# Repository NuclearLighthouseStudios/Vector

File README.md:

# Vector Hysteresis Distortion

These are the KiCAD schematics and board layout filed for my Vector Hysteresis Distortion pedal.  
If you just want the Gerber files or a PDF of the schematic check out the releases tab for downloads.

This PCB should be easily manufacturable with most online PCB houses by just uploading the gerber files.

This board is designed to be used with my Switchboard Pedal IO PCB which you can find [here](https://github.com/NuclearLighthouseStudios/Switchboard).

## BOM

| Reference       | Quantity | Value  | Description                                          |
| :-------------- | -------: | -----: | :--------------------------------------------------- |
| C1 C3 C5 C6 C7  | 5        | 100n   | WIMA MKS2 63V                                        |
| C2 C8           | 2        | 1µ     | WIMA MKS2 50V                                        |
| C4              | 1        | 470n   | WIMA MKS2 50V                                        |
| D1 D2           | 2        | 1N4148 | DO-35 Diode                                          |
| J1              | 1        |        | Pin Header, 6 pins, 2.54mm spacing                   |
| J2              | 1        |        | DC Barrel Jack with internal switch                  |
| Q1 Q2 Q3 Q4     | 4        | BC547B | 0.1A Ic, 45V Vce, Small Signal NPN Transistor, TO-92 |
| R1 R2 R5 R13    | 4        | 1M     | Metal film resistor 1%, DIN 0207                     |
| R3 R14          | 2        | 10k    | Metal film resistor 1%, DIN 0207                     |
| R4 R7 R8 R9 R12 | 5        | 100k   | Metal film resistor 1%, DIN 0207                     |
| R6 R10          | 2        | 470k   | Metal film resistor 1%, DIN 0207                     |
| R11             | 1        | 22k    | Metal film resistor 1%, DIN 0207                     |
| R15             | 1        | 39k    | Metal film resistor 1%, DIN 0207                     |
| RV1 RV2         | 2        | 100k   | Alps RK09K1130C94 Potentiometer                      |

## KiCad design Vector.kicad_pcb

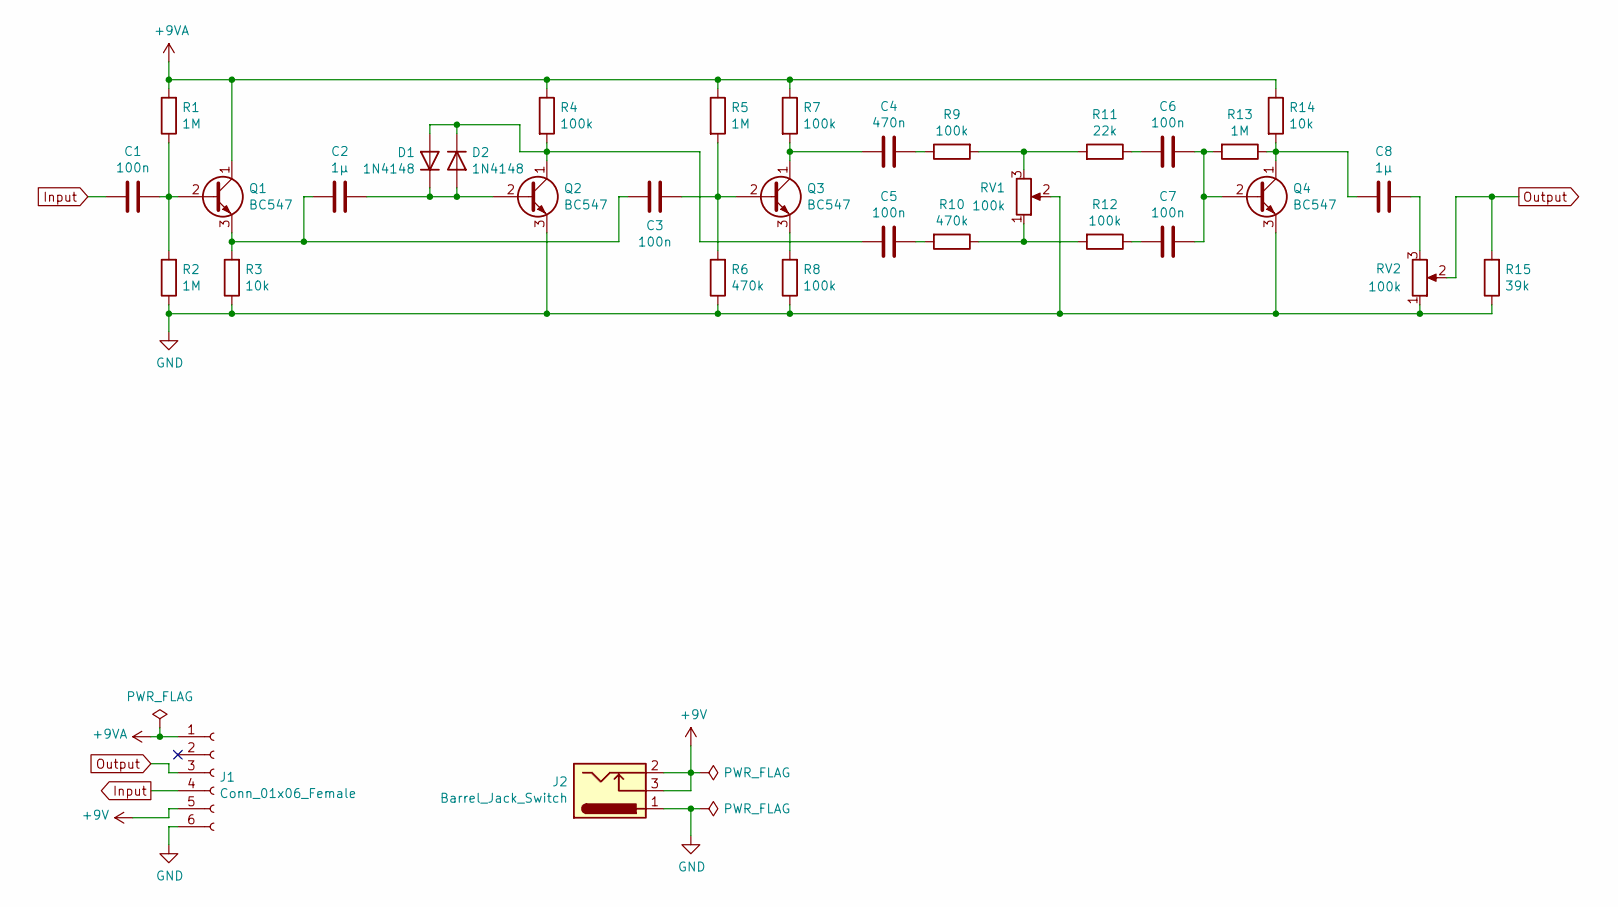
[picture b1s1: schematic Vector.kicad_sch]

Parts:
C1, C3, C5, C6, C7: 100n; C_Rect_L7.2mm_W2.5mm_P5.00mm_FKS2_FKP2_MKS2_MKP2
C2, C8: 1µ; C_Rect_L7.2mm_W4.5mm_P5.00mm_FKS2_FKP2_MKS2_MKP2
C4: 470n; C_Rect_L7.2mm_W3.5mm_P5.00mm_FKS2_FKP2_MKS2_MKP2
D1, D2: 1N4148; D_DO-35_SOD27_P2.54mm_Vertical_AnodeUp
J1: Conn_01x06_Female; PinHeader_1x06_P2.54mm_Vertical
J2: Barrel_Jack_Switch; BarrelJack_Horizontal_Short
Q1, Q2, Q3, Q4: BC547; TO-92_Wide
R1, R2, R5, R13: 1M; R_Axial_DIN0207_L6.3mm_D2.5mm_P2.54mm_Vertical
R3, R14: 10k; R_Axial_DIN0207_L6.3mm_D2.5mm_P2.54mm_Vertical
R4, R7, R8, R9: 100k; R_Axial_DIN0207_L6.3mm_D2.5mm_P2.54mm_Vertical
R6: 470k; R_Axial_DIN0207_L6.3mm_D2.5mm_P2.54mm_Vertical
R10: 470k; R_Axial_DIN0207_L6.3mm_D2.5mm_P7.62mm_Horizontal
R11: 22k; R_Axial_DIN0207_L6.3mm_D2.5mm_P7.62mm_Horizontal
R12: 100k; R_Axial_DIN0207_L6.3mm_D2.5mm_P7.62mm_Horizontal
R15: 39k; R_Axial_DIN0207_L6.3mm_D2.5mm_P7.62mm_Horizontal
RV1, RV2: 100k; Potentiometer_Alps_RK09K_Single_Vertical

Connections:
+9V: J1.5, J2.2, J2.3
+9VA: J1.1, Q1.1 (C), R1.2, R4.1, R5.1, R7.1, R14.1
GND: J1.6, J2.1, Q2.3 (E), Q4.3 (E), R2.1, R3.1, R6.1, R8.1, R15.1, RV1.2, RV2.1
Input: C1.2, J1.4
unnamed: C1.1, Q1.2 (B), R1.1, R2.2
unnamed: C2.1, C3.2, Q1.3 (E), R3.2
unnamed: C2.2, D1.1 (K), D2.2 (A), Q2.2 (B)
unnamed: C3.1, Q3.2 (B), R5.2, R6.2
unnamed: C4.1, R9.1
unnamed: C4.2, Q3.1 (C), R7.2
unnamed: C5.1, R10.2
unnamed: C5.2, D1.2 (A), D2.1 (K), Q2.1 (C), R4.2
unnamed: C6.1, C7.1, Q4.2 (B), R13.2
unnamed: C6.2, R11.1
unnamed: C7.2, R12.1
unnamed: C8.1, RV2.3
unnamed: C8.2, Q4.1 (C), R13.1, R14.2
unnamed: Q3.3 (E), R8.2
unnamed: R10.1, R12.2, RV1.1
unnamed: R9.2, R11.2, RV1.3
Output: J1.3, R15.2, RV2.2

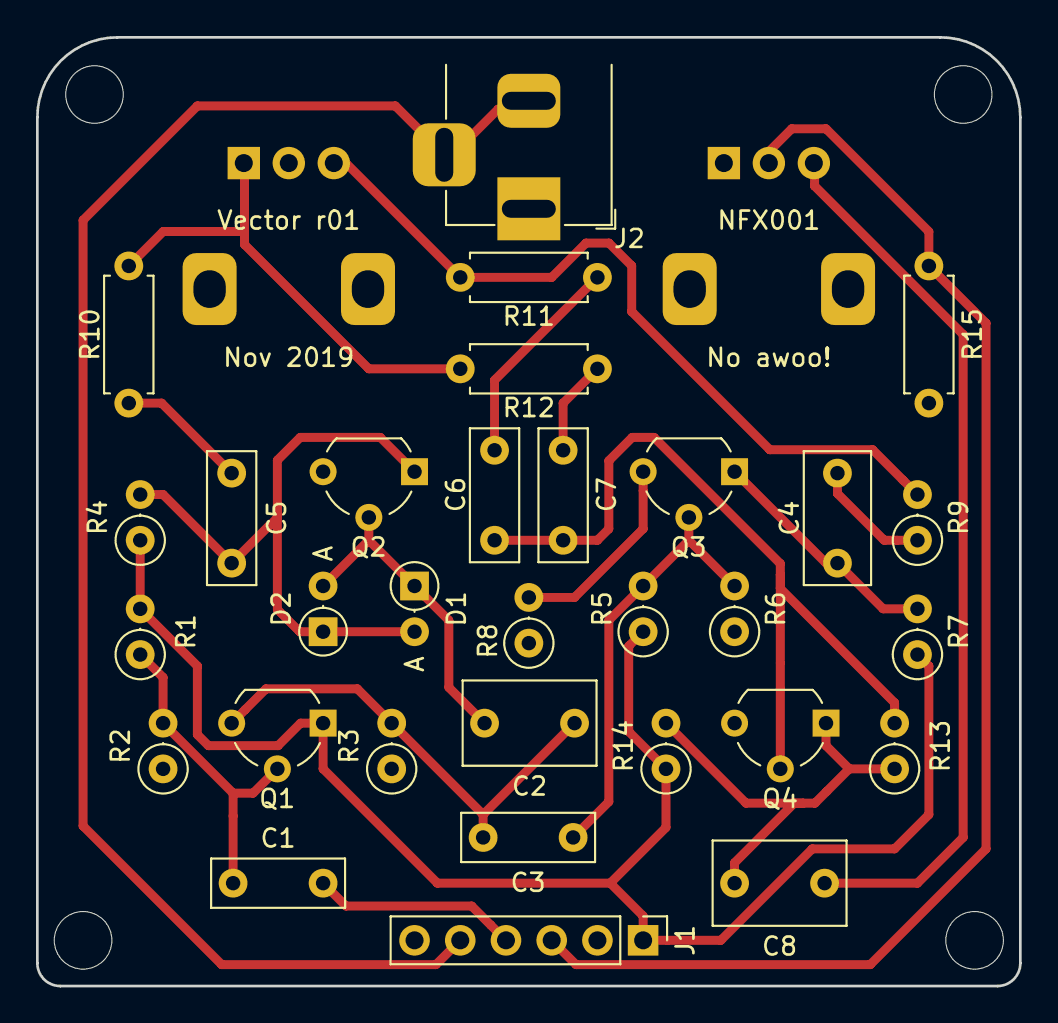
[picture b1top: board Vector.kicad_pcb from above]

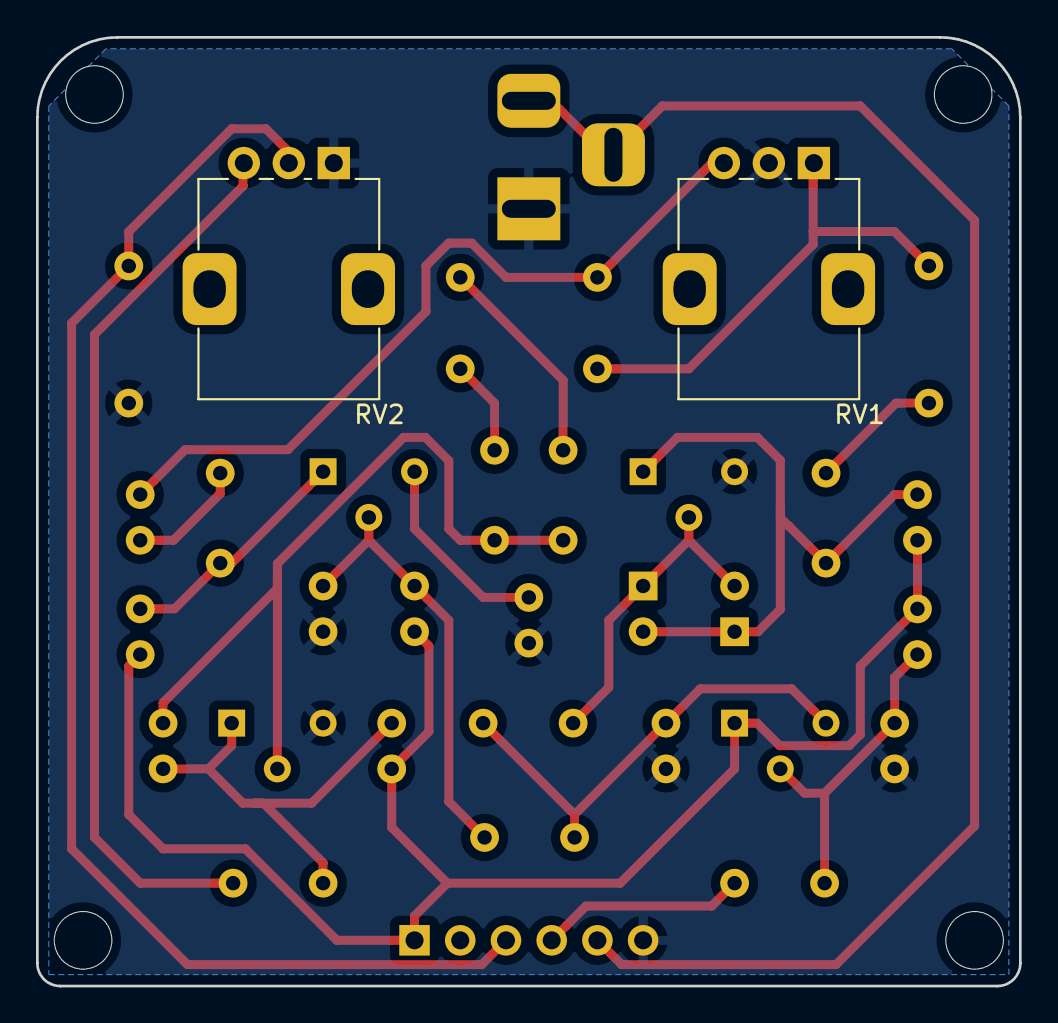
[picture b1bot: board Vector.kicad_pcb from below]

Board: 2 copper layers, 54.6 x 52.7 mm, 33 parts (2 on the bottom side), 21 nets.

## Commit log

2020-12-30 Open Source, yay!
2020-12-31 Fix cap voltages
2022-08-14 Migrate to KiCAD 6
2022-08-14 Remove unused footprint libraries
2022-08-14 Update symbols/footprints from libraries
2022-08-14 Fix DRC errors

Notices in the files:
Vector.kicad_pcb:
CC BY-NC-SA
